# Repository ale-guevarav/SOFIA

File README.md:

# SOFIA

Superficie cinética de 16 unidades hexagonales (2 grados de libertad cada una) que responde a los gestos de una persona. Proyecto del Laboratorio de Desarrollo de Soluciones Tecnológicas, ITESO.

| Carpeta | Qué tiene | Léeme |
| --- | --- | --- |
| `Vision/` | Detección de posturas y de la mano (MediaPipe), GUI (PySide6), enlace BLE con el ESP32 y menú **Alineación** | [`Vision/README.md`](Vision/README.md) |
| `Alignment/` | Diagnóstico de alineación con cámara: CNN, método geométrico, app y entrenamiento | [`Alignment/README.md`](Alignment/README.md) |
| `ESP32/` | Firmware del maestro (BLE + 16 unidades) y de los esclavos (RS-485/Modbus); prueba de ángulos al azar | [`ESP32/README.md`](ESP32/README.md) |
| `Webots/` | Simulación de las 16 unidades (gemelo digital) y mundos del dataset de alineación | [`Webots/README.md`](Webots/README.md) |
| `PCB/` | PCB de SOFIA (KiCad) | |
| `Paper-Latex/` | Papers y manual de usuario | |
| `Respuesta revisores/` | Respuestas a los revisores de cada corte | |

```
Cámara de poses ──► Vision (GUI) ──BLE──► ESP32 maestro ──► 16 unidades
                        │   └──TCP──► Webots (simulación)
Cámara del módulo ──► Alineación (CNN de Alignment/) ──► ceros de los servos (AJUSTE)
```

Todo se corre desde esta carpeta con el entorno de Python activado (ver la instalación en cada léeme). Un solo `.gitignore` en la raíz cubre todo el repositorio.

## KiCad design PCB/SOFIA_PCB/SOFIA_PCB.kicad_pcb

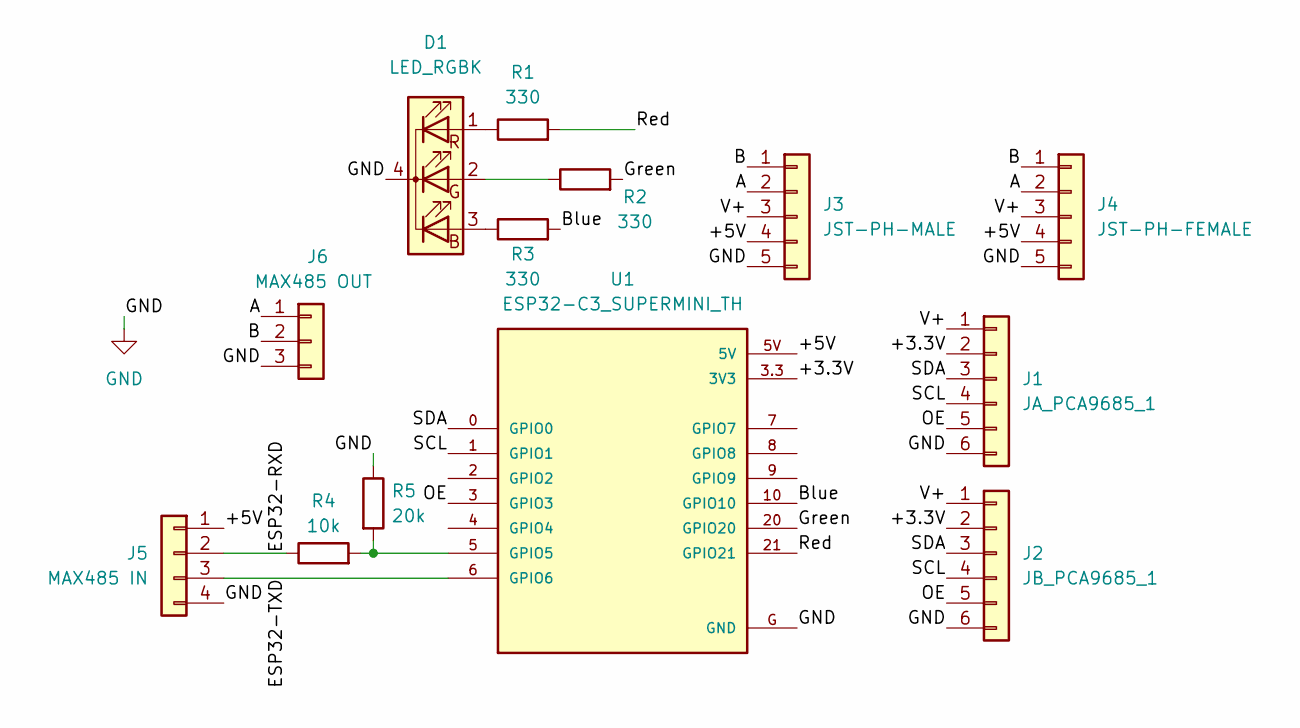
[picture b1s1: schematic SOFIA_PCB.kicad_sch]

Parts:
D1: LED_RGBK; LED_D5.0mm-4_RGB_Wide_Pins
J1: JA_PCA9685_1; PinHeader_1x06_P2.54mm_Vertical
J2: JB_PCA9685_1; PinHeader_1x06_P2.54mm_Vertical
J3: JST-PH-MALE; JST_PH_B5B-PH-K_1x05_P2.00mm_Vertical
J4: JST-PH-FEMALE; JST_PH_B5B-PH-K_1x05_P2.00mm_Vertical
J5: MAX485 IN; PinHeader_1x04_P2.54mm_Vertical
J6: MAX485 OUT; PinHeader_1x03_P2.54mm_Vertical
R1, R2, R3: 330; R_Axial_DIN0207_L6.3mm_D2.5mm_P10.16mm_Horizontal
R4: 10k; R_Axial_DIN0207_L6.3mm_D2.5mm_P10.16mm_Horizontal
R5: 20k; R_Axial_DIN0207_L6.3mm_D2.5mm_P10.16mm_Horizontal
U1: ESP32-C3_SUPERMINI_TH; MODULE_ESP32-C3_SUPERMINI_TH

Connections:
/+3.3V: J1.2, J2.2, U1.3.3 (3V3)
/+5V: J3.4, J4.4, J5.1, U1.5V
/A: J3.2, J4.2, J6.1
/B: J3.1, J4.1, J6.2
/Blue: R3.2, U1.10 (GPIO10)
/ESP32-RXD: J5.2, R4.1
/ESP32-TXD: J5.3, U1.6 (GPIO6)
/Green: R2.2, U1.20 (GPIO20)
/OE: J1.5, J2.5, U1.3 (GPIO3)
/Red: R1.2, U1.21 (GPIO21)
/SCL: J1.4, J2.4, U1.1 (GPIO1)
/SDA: J1.3, J2.3, U1.0 (GPIO0)
/V+: J1.1, J2.1, J3.3, J4.3
GND: D1.4 (K), J1.6, J2.6, J3.5, J4.5, J5.4, J6.3, R5.1, U1.G (GND)
unnamed: D1.3 (BA), R3.1
unnamed: D1.2 (GA), R2.1
unnamed: D1.1 (RA), R1.1
unnamed: R4.2, R5.2, U1.5 (GPIO5)

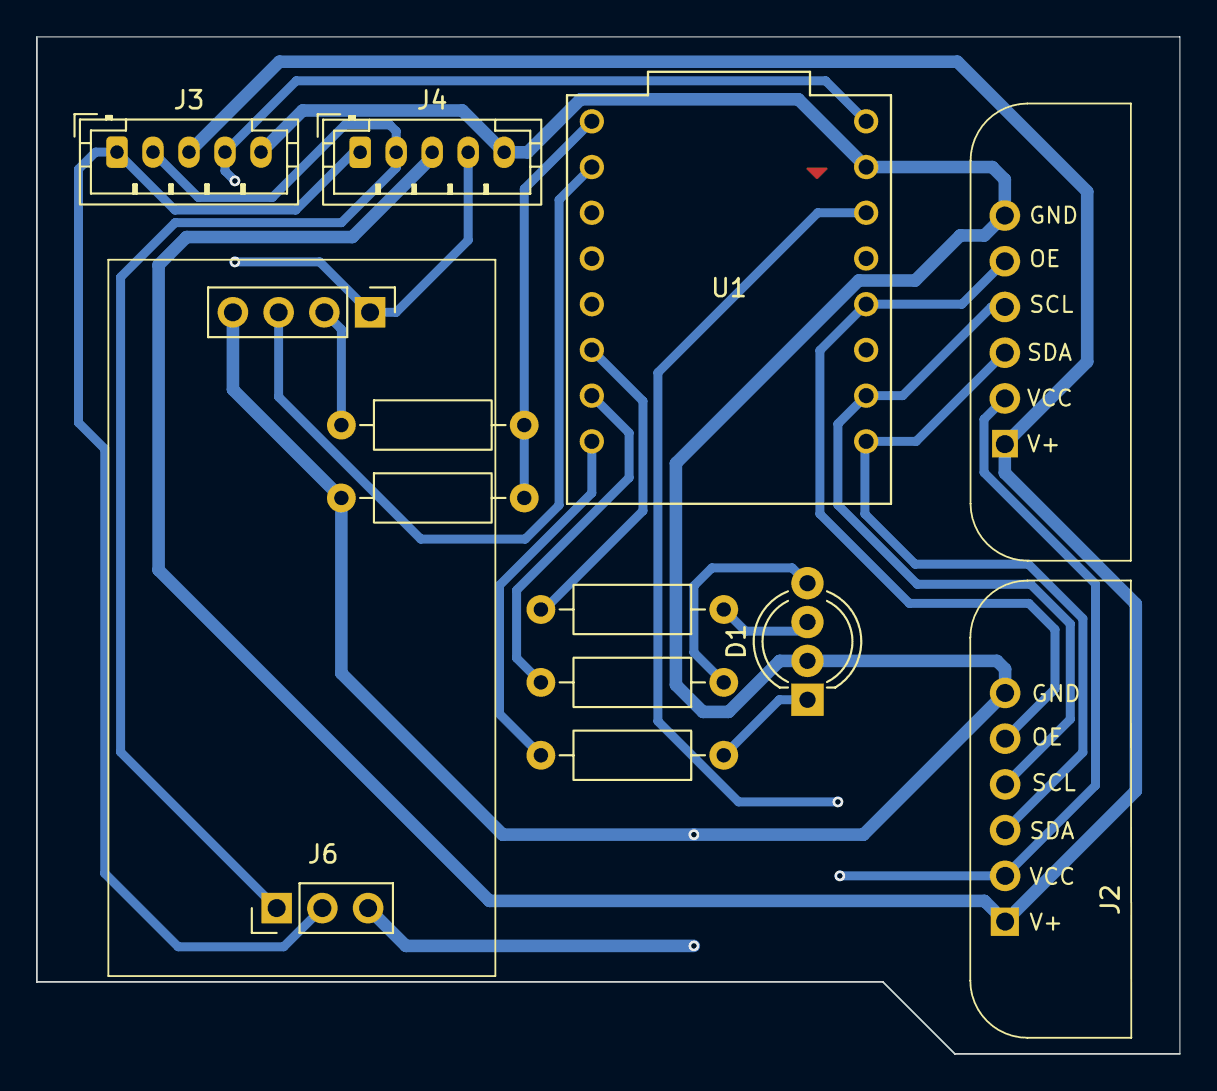
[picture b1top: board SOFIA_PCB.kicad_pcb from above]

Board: 2 copper layers, 63.5 x 56.5 mm, 13 parts (0 on the bottom side), 18 nets.

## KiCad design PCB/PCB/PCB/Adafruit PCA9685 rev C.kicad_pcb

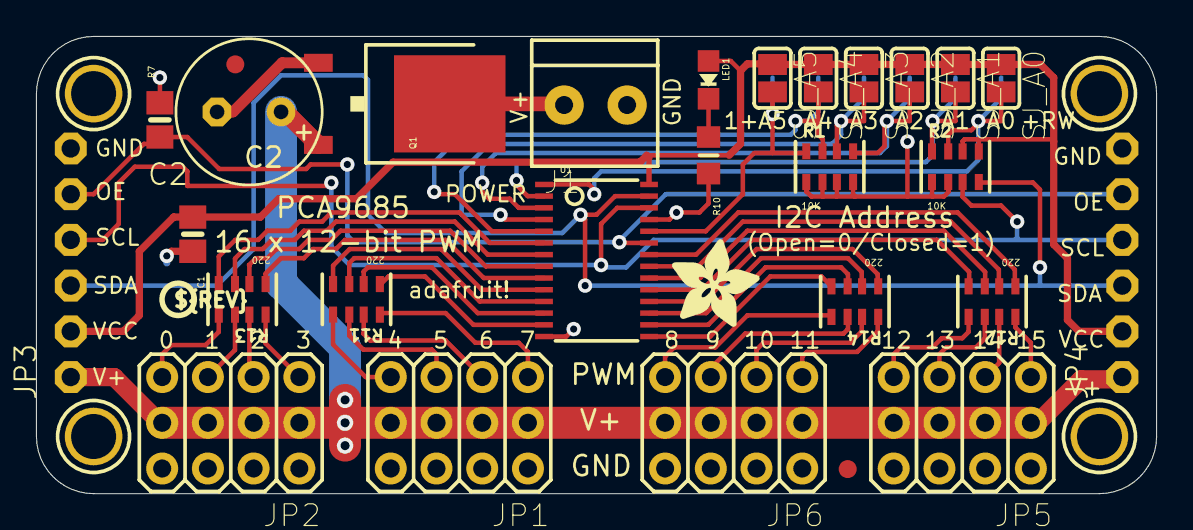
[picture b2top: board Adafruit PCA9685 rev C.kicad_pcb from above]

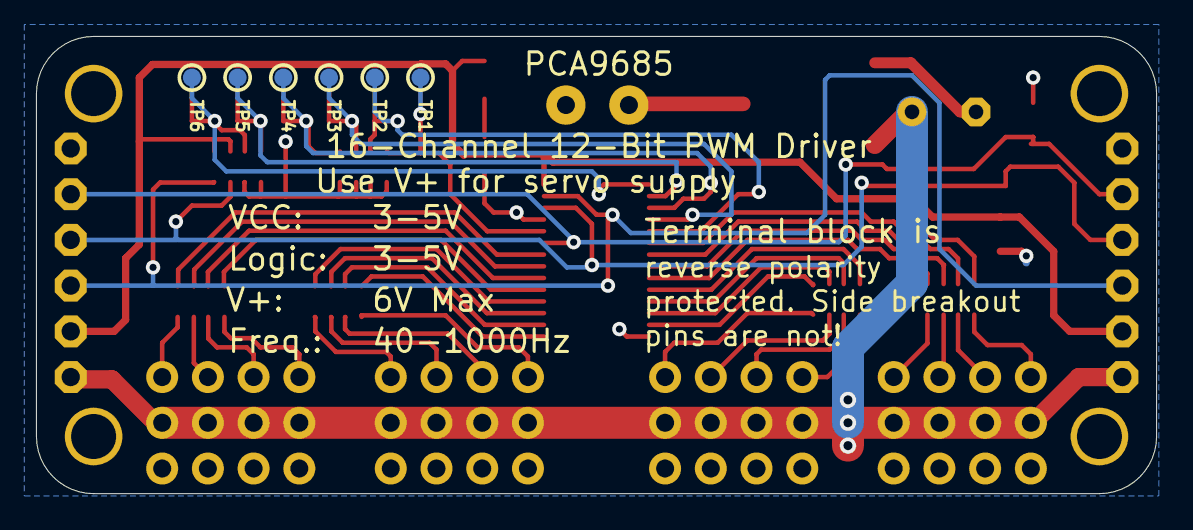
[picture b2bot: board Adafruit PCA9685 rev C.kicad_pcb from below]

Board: 2 copper layers, 62.2 x 25.4 mm, 40 parts (6 on the bottom side), 46 nets.

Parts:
C1: 10uF; 0805-NO
C2: E3,5-8
FID1, FID2: FIDUCIAL""; FIDUCIAL_1MM
J1: TERMBLOCK_1X2-3.5MM
JP1, JP2, JP5, JP6: 3X04
JP3, JP4: 1X06-CLEANBIG
LED1: GREEN; CHIPLED_0805_NOOUTLINE
Q1: AOD417; TO252
R1, R2: 10K; RESPACK_4X0603
R7: 10K; 0805-NO
R10: 470; _0805MP
R11, R12, R13, R14: 220; RESPACK_4X0603
SJ_A0, SJ_A1, SJ_A2, SJ_A3, SJ_A4, SJ_A5: SOLDERJUMPER_REFLOW_NOPASTE
TP1, TP2, TP3, TP4, TP5, TP6: TESTPOINT_ROUND_1MM
U1: PCA9685; TSSOP28
U$47, U$48, U$49, U$50: MOUNTINGHOLE2.5; MOUNTINGHOLE_2.5_PLATED
U$51: ADAFRUIT_5MM
U$54: PCBFEAT-REV-040

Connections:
5.0V: C2.+, JP1.2, JP1.5, JP1.8, JP1.11, JP2.2, JP2.5, JP2.8, JP2.11, JP3.1, JP4.1, JP5.2, JP5.5, JP5.8, JP5.11, JP6.2, JP6.5, JP6.8, JP6.11, Q1.2
A0: R2.7, SJ_A0.2, TP6.P$1, U1.1
A1: R2.8, SJ_A1.2, TP5.P$1, U1.2
A2: R1.5, SJ_A2.2, TP4.P$1, U1.3
A3: R1.6, SJ_A3.2, TP3.P$1, U1.4
A4: R1.7, SJ_A4.2, TP2.P$1, U1.5
A5: R1.8, SJ_A5.2, TP1.P$1, U1.24
GND: C1.2, C2.-, J1.2, JP1.3, JP1.6, JP1.9, JP1.12, JP2.3, JP2.6, JP2.9, JP2.12, JP3.6, JP4.6, JP5.3, JP5.6, JP5.9, JP5.12, JP6.3, JP6.6, JP6.9, JP6.12, Q1.1, R1.1, R1.2, R1.3, R1.4, R2.1, R2.2, R7.2, R10.2, U1.14, U1.25
unnamed: LED1.C, R10.1
unnamed: JP1.4, R11.7
unnamed: JP1.1, R11.8
unnamed: JP1.7, R11.6
unnamed: JP1.10, R11.5
unnamed: JP2.1, R13.8
unnamed: JP2.4, R13.7
unnamed: JP2.7, R13.6
unnamed: JP2.10, R13.5
unnamed: JP6.10, R14.5
unnamed: JP6.7, R14.6
unnamed: JP6.4, R14.7
unnamed: JP6.1, R14.8
unnamed: JP5.10, R12.5
unnamed: JP5.7, R12.6
unnamed: JP5.4, R12.7
unnamed: JP5.1, R12.8
OE: JP3.5, JP4.5, R7.1, U1.23
PWM0: R13.4, U1.6
PWM1: R13.3, U1.7
PWM2: R13.2, U1.8
PWM3: R13.1, U1.9
PWM4: R11.4, U1.10
PWM5: R11.3, U1.11
PWM6: R11.2, U1.12
PWM7: R11.1, U1.13
PWM8: R14.4, U1.15
PWM9: R14.3, U1.16
PWM10: R14.2, U1.17
PWM11: R14.1, U1.18
PWM12: R12.4, U1.19
PWM13: R12.3, U1.20
PWM14: R12.2, U1.21
PWM15: R12.1, U1.22
PWRIN: J1.1, Q1.3
SCL: JP3.4, JP4.4, R2.3, U1.26
SDA: JP3.3, JP4.3, R2.4, U1.27
VCC: C1.1, JP3.2, JP4.2, LED1.A, R2.5, R2.6, SJ_A0.1, SJ_A1.1, SJ_A2.1, SJ_A3.1, SJ_A4.1, SJ_A5.1, U1.28
